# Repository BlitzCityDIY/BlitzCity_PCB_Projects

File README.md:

# BlitzCity_PCB_Projects
Projects with PCB files

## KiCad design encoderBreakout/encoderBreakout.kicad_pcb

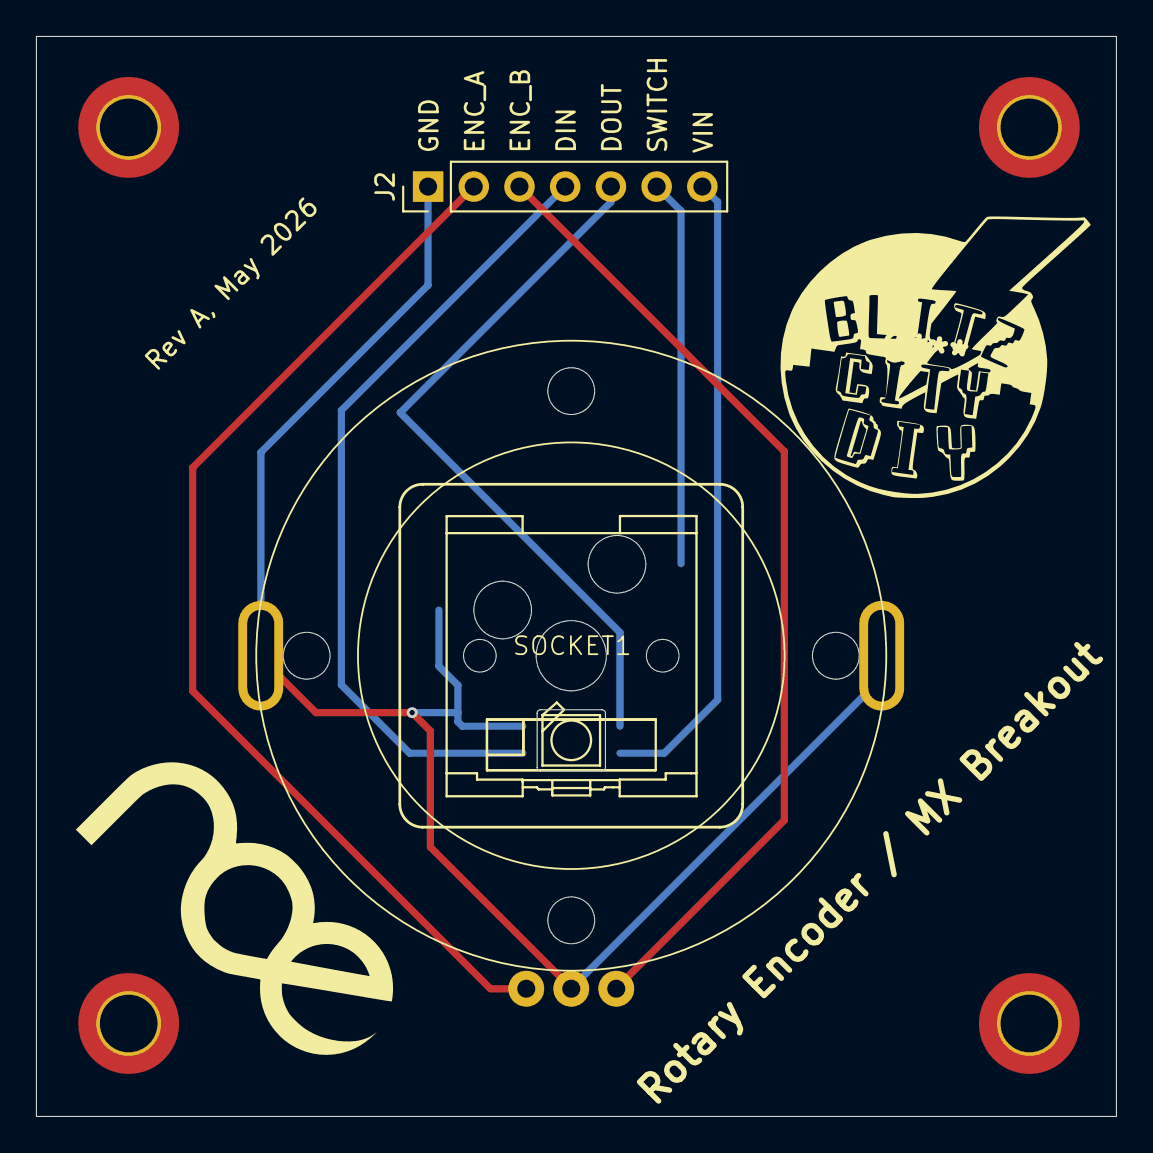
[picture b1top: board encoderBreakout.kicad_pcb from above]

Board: 2 copper layers, 60.0 x 60.0 mm, 4 parts (0 on the bottom side), 7 nets.

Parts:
ENC1: EC35A_nosocket
J2: Conn_01x07_Pin; PinHeader_1x07_P2.54mm_Vertical
REV_NEOPIXEL1: reverse_neopixel
SOCKET1: kailh_socket

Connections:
+3.3V: J2.7, REV_NEOPIXEL1.1-VDD
/ENC_A: ENC1.A, J2.2
/ENC_B: ENC1.B, J2.3
/NEO_DIN: J2.4, REV_NEOPIXEL1.4-DIN
/NEO_DOUT: J2.5, REV_NEOPIXEL1.2-DOUT
/SWITCH: J2.6, SOCKET1.SW_1
GND: ENC1.C, ENC1.G0, ENC1.G1, J2.1, REV_NEOPIXEL1.3-GND, SOCKET1.SW_2

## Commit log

2025-06-06 adding pocket operator files
2025-06-06 excel to csv
2025-06-06 Update code.py
    license
2025-06-06 Create LICENSE
    MIT
2025-06-20 adding bff squad
2025-06-23 add midi roundabout
2025-06-30 adding nixie newxie shield
2025-07-01 comment out serial port wait
2025-11-25 adding pi pc files
2025-11-25 Update README.md with external links
    Added external links section with Printables download.
2026-04-30 kicad part, encoder project
2026-04-30 gitignore
2026-05-06 encoder breakout rev a
2026-05-06 gitignore cleanup
